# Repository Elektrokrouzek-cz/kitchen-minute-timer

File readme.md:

# Kitchen minute timer
This is the construction of simple kitchen minute timer based on logical 
circuits (4060, 4040, 4081 and 2x 4017). It was designed for beginners to 
train SMD components soldering (all passive components have 1206 packages).

PCB is 4-layer and was designed using KiCad 8. Fabrication output for JLCPCB is in gerber folder.

Happy soldering!

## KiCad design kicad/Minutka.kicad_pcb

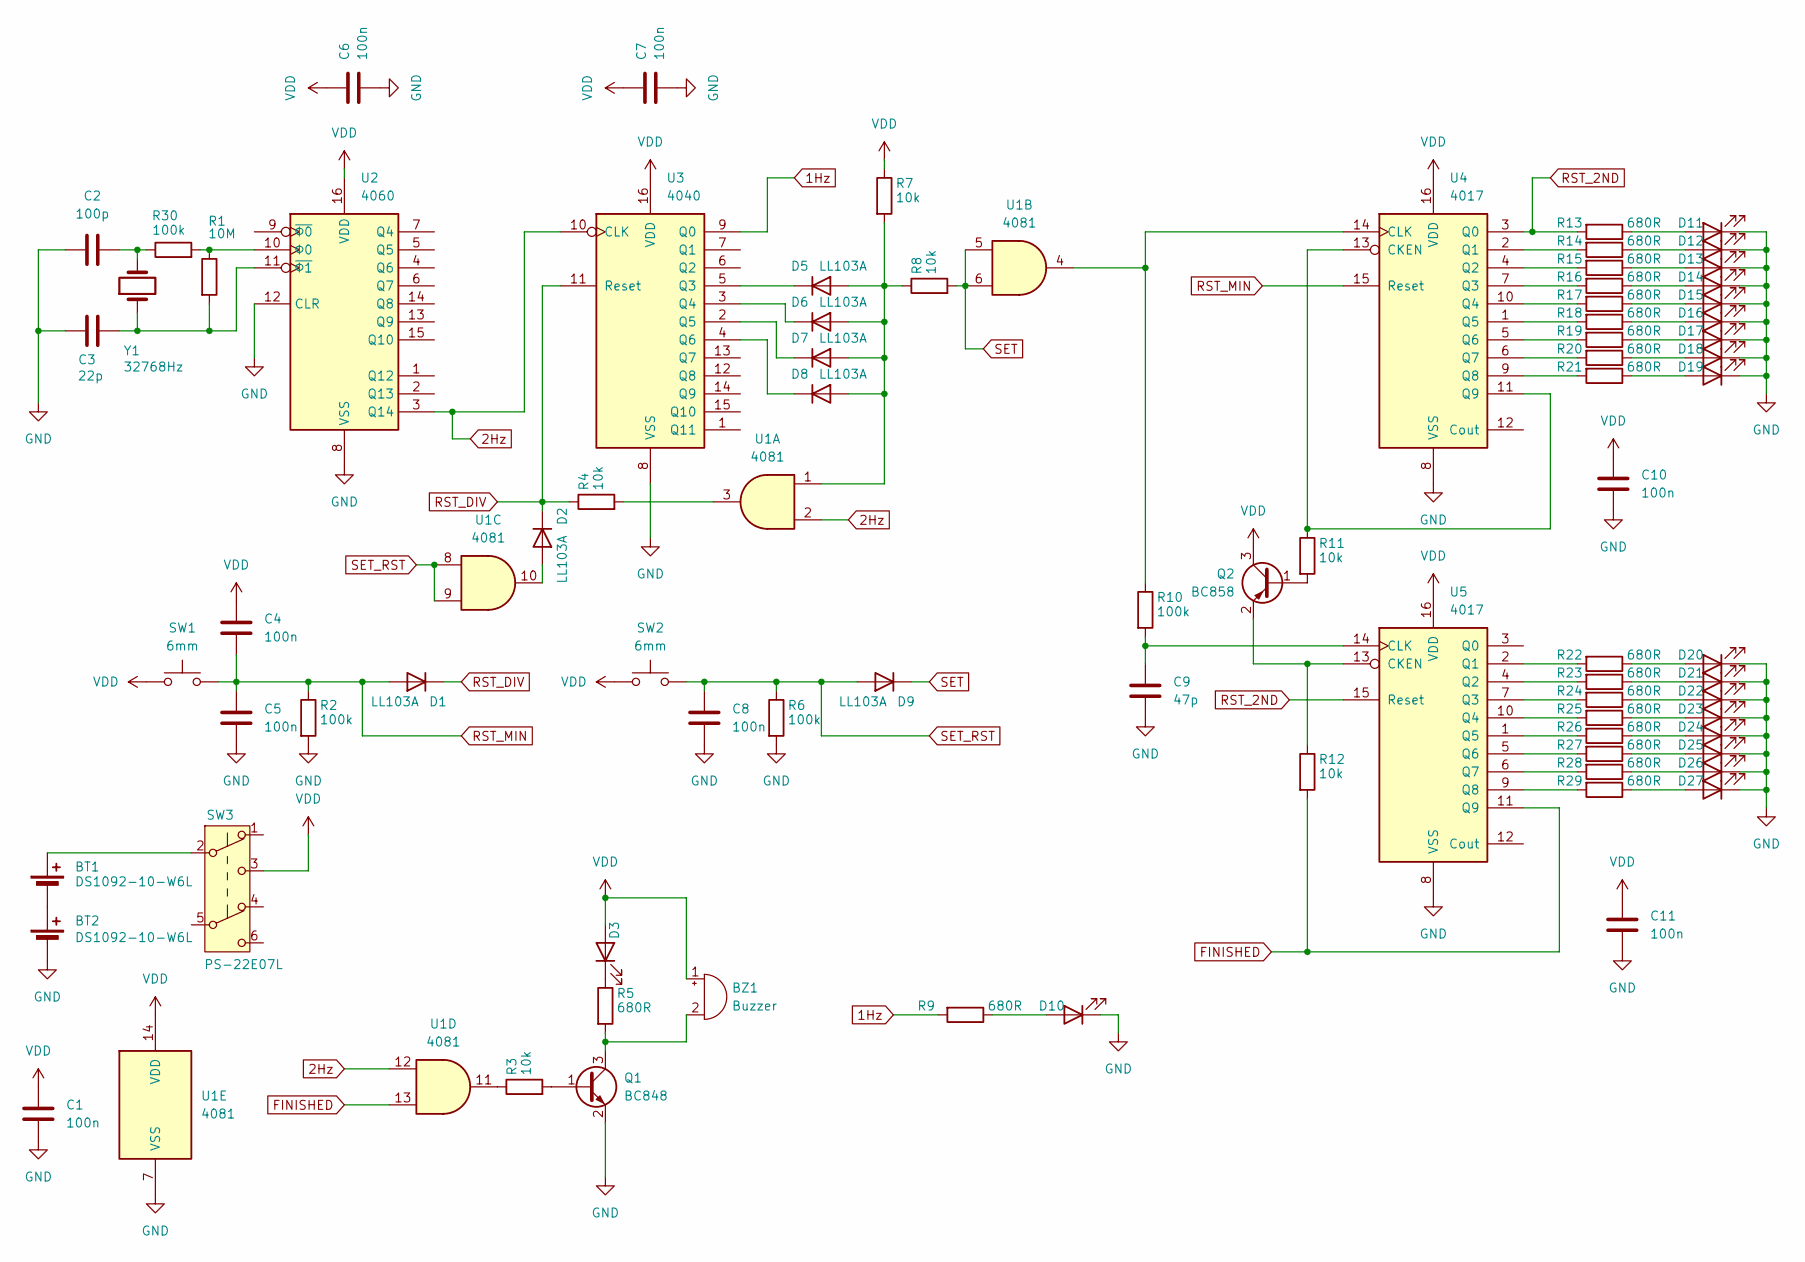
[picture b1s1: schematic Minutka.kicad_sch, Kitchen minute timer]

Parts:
BT1, BT2: DS1092-10-W6L; BatteryHolder_Renata_SMTU2032-LF_1x2032
BZ1: Buzzer; MagneticBuzzer_ProSignal_ABI-010-RC
C1, C4, C5, C6, C7, C8, C10, C11: 100n; C_1206_3216Metric_Pad1.33x1.80mm_HandSolder
C2: 100p; C_1206_3216Metric_Pad1.33x1.80mm_HandSolder
C3: 22p; C_1206_3216Metric_Pad1.33x1.80mm_HandSolder
C9: 47p; C_1206_3216Metric_Pad1.33x1.80mm_HandSolder
D1, D2, D5, D6, D7, D8, D9: LL103A; D_MiniMELF
D3: 3mm R; LED_D3.0mm
D10: 3mm Y; LED_D3.0mm
D11, D12, D13, D14, D15, D16, D17, D18, D19, D20, D21, D22, D23, D24, D25, D26, D27: 3mm G; LED_D3.0mm
Q1: BC848; SOT-23
Q2: BC858; SOT-23
R1: 10M; R_1206_3216Metric_Pad1.30x1.75mm_HandSolder
R2, R6, R10, R30: 100k; R_1206_3216Metric_Pad1.30x1.75mm_HandSolder
R3, R4, R7, R8, R11, R12: 10k; R_1206_3216Metric_Pad1.30x1.75mm_HandSolder
R5, R9, R13, R14, R15, R16, R17, R18, R19, R20, R21, R22, R23, R24, R25, R26, R27, R28, R29: 680R; R_1206_3216Metric_Pad1.30x1.75mm_HandSolder
SW1, SW2: 6mm; SW_PUSH_6mm_H13mm
SW3: PS-22E07L; SW_DPDT_7x7_Turbo
U1: 4081; SO-14_3.9x8.65mm_P1.27mm
U2: 4060; SO-16_3.9x9.9mm_P1.27mm
U3: 4040; SO-16_3.9x9.9mm_P1.27mm
U4, U5: 4017; SO-16_3.9x9.9mm_P1.27mm
Y1: 32768Hz; Crystal_AT310_D3.0mm_L10.0mm_Horizontal

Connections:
1Hz: R9.2, U3.9 (Q0)
2Hz: U1.2, U1.12, U2.3 (Q14), U3.10 (CLK)
FINISHED: R12.2, U1.13, U5.11 (Q9)
GND: BT2.2 (-), C1.1, C2.1, C3.1, C5.1, C6.1, C7.1, C8.1, C9.1, C10.1, C11.1, D10.1 (K), D11.1 (K), D12.1 (K), D13.1 (K), D14.1 (K), D15.1 (K), D16.1 (K), D17.1 (K), D18.1 (K), D19.1 (K), D20.1 (K), D21.1 (K), D22.1 (K), D23.1 (K), D24.1 (K), D25.1 (K), D26.1 (K), D27.1 (K), Q1.2 (E), R2.2, R6.2, U1.7 (VSS), U2.8 (VSS), U2.12 (CLR), U3.8 (VSS), U4.8 (VSS), U5.8 (VSS)
unnamed: BT1.1 (+), SW3.2 (B)
unnamed: BT1.2 (-), BT2.1 (+)
unnamed: BZ1.2 (-), Q1.3 (C), R5.2
unnamed: C2.2, R30.1, Y1.2
unnamed: D2.2 (A), U1.10
unnamed: D3.1 (K), R5.1
unnamed: D5.2 (A), D6.2 (A), D7.2 (A), D8.2 (A), R7.2, R8.1, U1.1
unnamed: D5.1 (K), U3.5 (Q3)
unnamed: D6.1 (K), U3.3 (Q4)
unnamed: D7.1 (K), U3.2 (Q5)
unnamed: D8.1 (K), U3.4 (Q6)
unnamed: D10.2 (A), R9.1
unnamed: D11.2 (A), R13.1
unnamed: D12.2 (A), R14.1
unnamed: D13.2 (A), R15.1
unnamed: D14.2 (A), R16.1
unnamed: D15.2 (A), R17.1
unnamed: D16.2 (A), R18.1
unnamed: D17.2 (A), R19.1
unnamed: D18.2 (A), R20.1
unnamed: D19.2 (A), R21.1
unnamed: D20.2 (A), R22.1
unnamed: D21.2 (A), R23.1
unnamed: D22.2 (A), R24.1
unnamed: D23.2 (A), R25.1
unnamed: D24.2 (A), R26.1
unnamed: D25.2 (A), R27.1
unnamed: D26.2 (A), R28.1
unnamed: D27.2 (A), R29.1
unnamed: Q1.1 (B), R3.2
unnamed: Q2.1 (B), R11.2
unnamed: Q2.2 (E), R12.1, U5.13 (CKEN)
unnamed: R3.1, U1.11
unnamed: R4.2, U1.3
unnamed: C3.2, R1.2, U2.11 (~Φ1), Y1.1
unnamed: R1.1, R30.2, U2.10 (Φ0)
unnamed: R11.1, U4.11 (Q9), U4.13 (CKEN)
unnamed: R10.1, U1.4, U4.14 (CLK)
unnamed: R14.2, U4.2 (Q1)
unnamed: R15.2, U4.4 (Q2)
unnamed: R16.2, U4.7 (Q3)
unnamed: R17.2, U4.10 (Q4)
unnamed: R18.2, U4.1 (Q5)
unnamed: R19.2, U4.5 (Q6)
unnamed: R20.2, U4.6 (Q7)
unnamed: R21.2, U4.9 (Q8)
unnamed: C9.2, R10.2, U5.14 (CLK)
unnamed: R22.2, U5.2 (Q1)
unnamed: R23.2, U5.4 (Q2)
unnamed: R24.2, U5.7 (Q3)
unnamed: R25.2, U5.10 (Q4)
unnamed: R26.2, U5.1 (Q5)
unnamed: R27.2, U5.5 (Q6)
unnamed: R28.2, U5.6 (Q7)
unnamed: R29.2, U5.9 (Q8)
RST_2ND: R13.2, U4.3 (Q0), U5.15 (Reset)
RST_DIV: D1.1 (K), D2.1 (K), R4.1, U3.11 (Reset)
RST_MIN: C4.1, C5.2, D1.2 (A), R2.1, SW1.2, U4.15 (Reset)
SET: D9.1 (K), R8.2, U1.5, U1.6
SET_RST: C8.2, D9.2 (A), R6.1, SW2.2, U1.8, U1.9
VDD: BZ1.1 (+), C1.2, C4.2, C6.2, C7.2, C10.2, C11.2, D3.2 (A), Q2.3 (C), R7.1, SW1.1, SW2.1, SW3.3 (C), U1.14 (VDD), U2.16 (VDD), U3.16 (VDD), U4.16 (VDD), U5.16 (VDD)

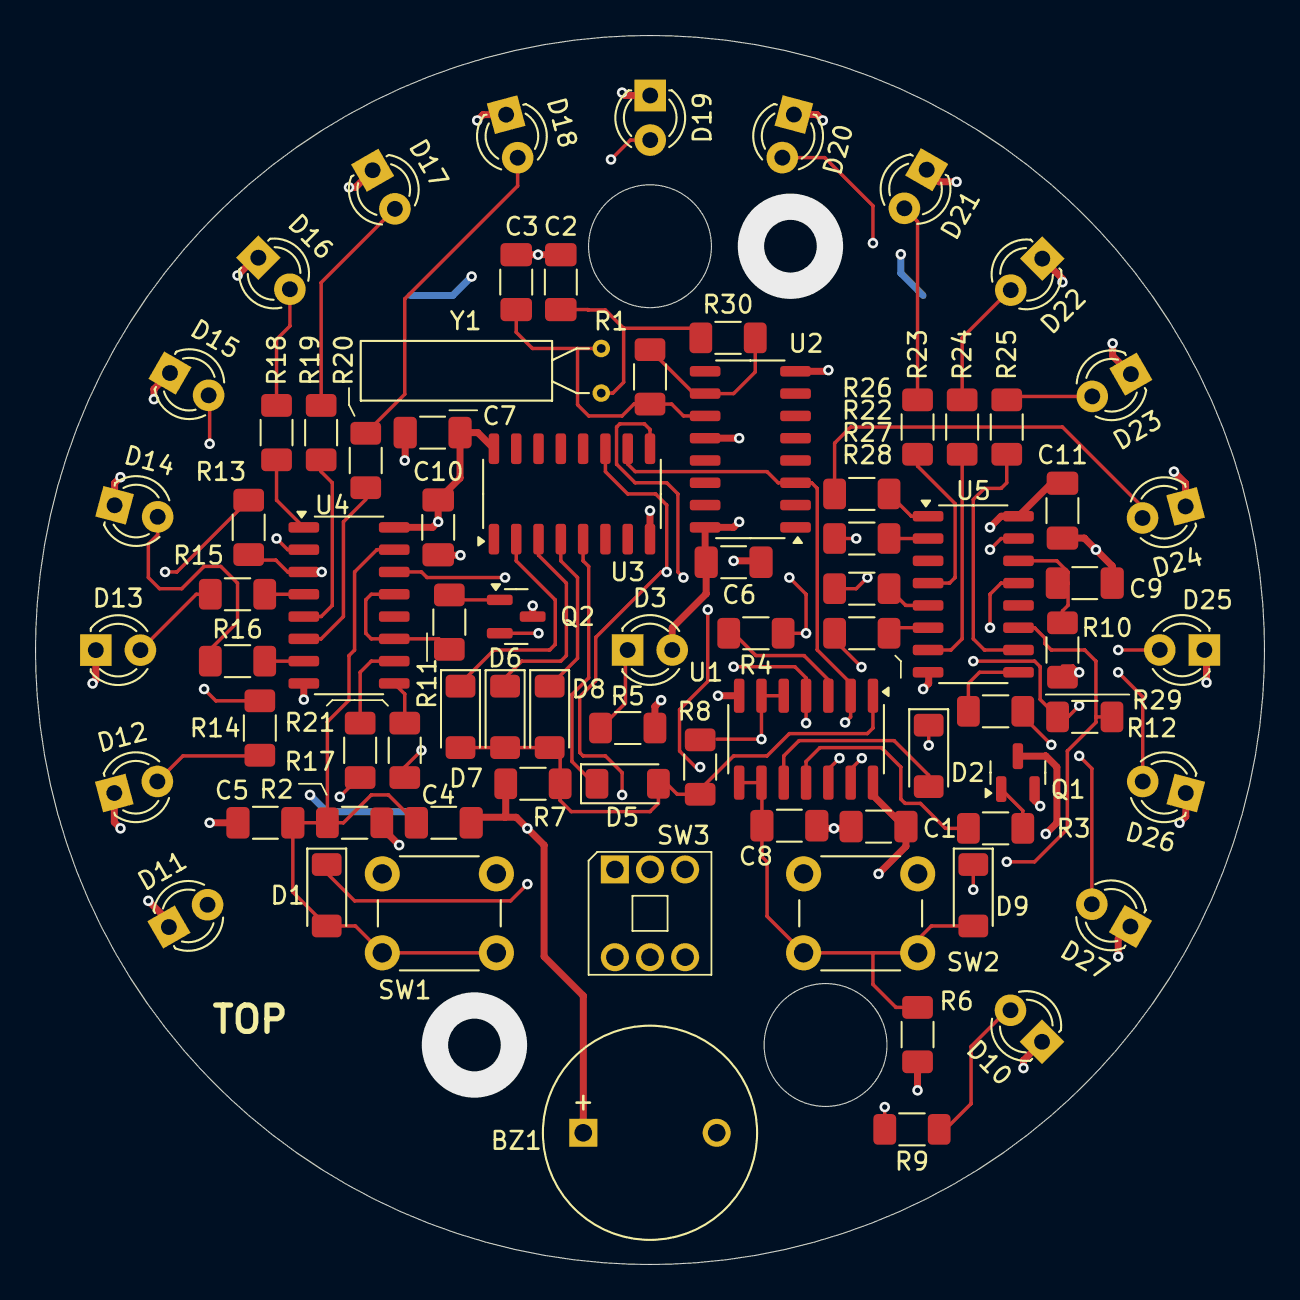
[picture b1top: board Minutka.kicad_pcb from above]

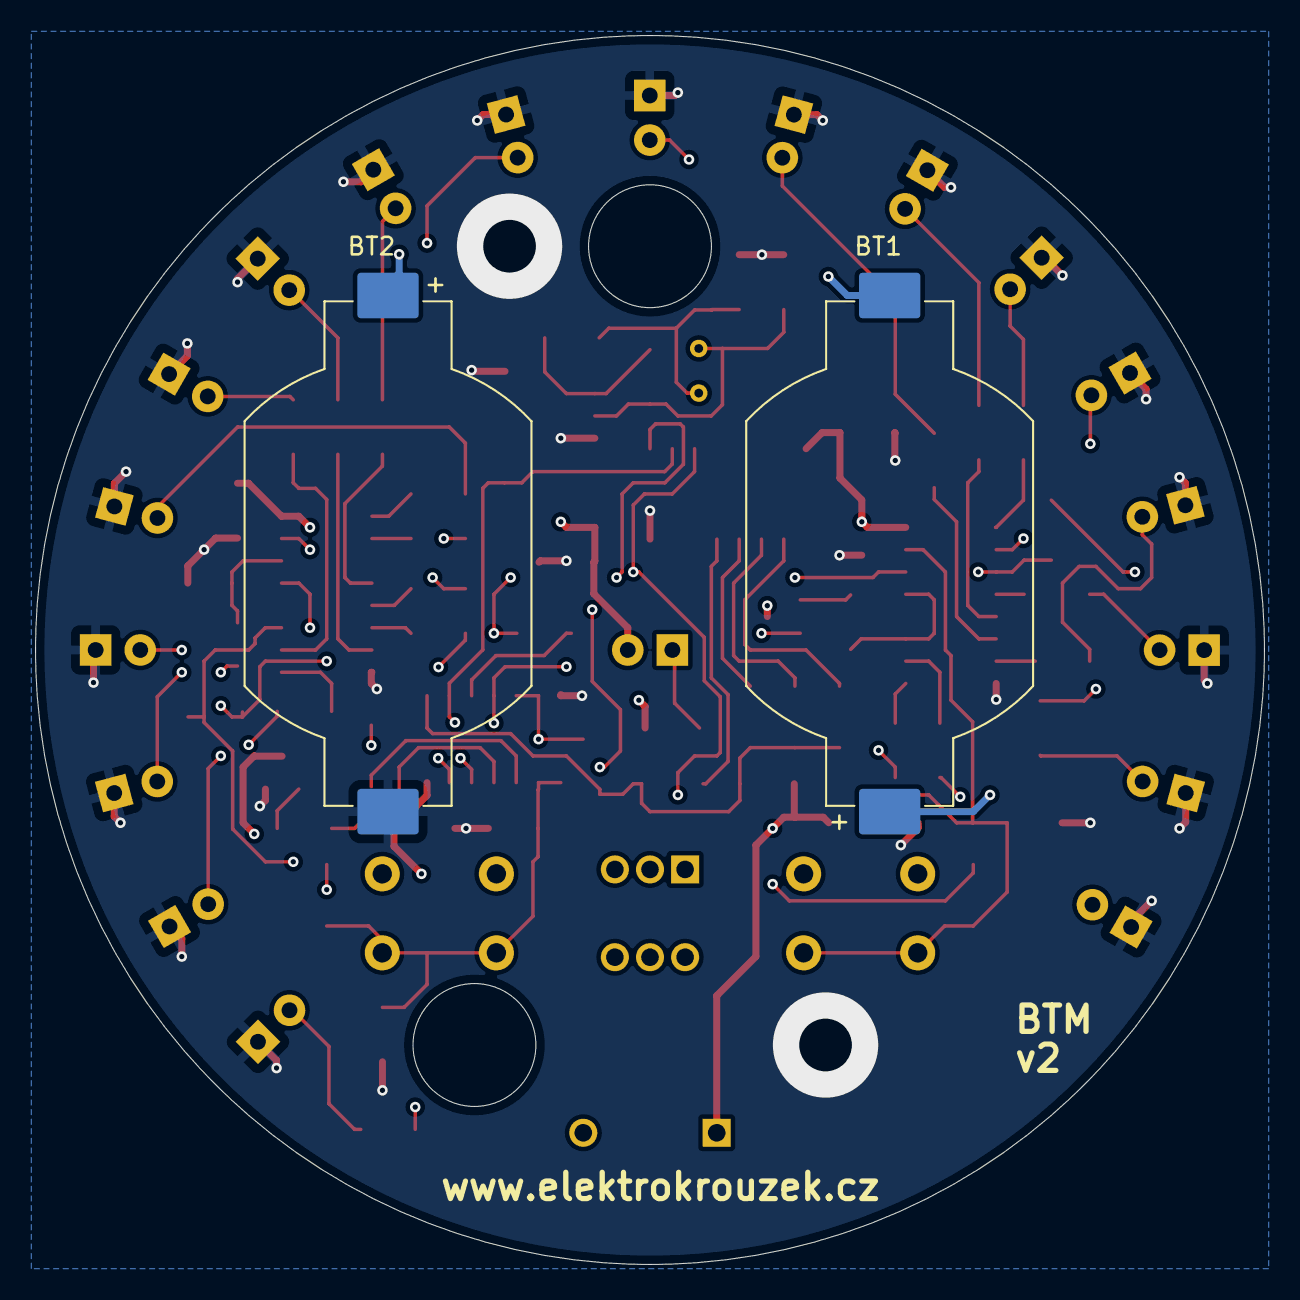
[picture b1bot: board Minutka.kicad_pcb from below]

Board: 4 copper layers, 70.0 x 70.0 mm, 81 parts (2 on the bottom side), 65 nets.

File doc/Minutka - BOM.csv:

"Reference","Value","Footprint","Qty","DNP"
"BT1,BT2","DS1092-10-W6L","Battery:BatteryHolder_Renata_SMTU2032-LF_1x2032","2",""
"BZ1","Buzzer","Buzzer_Beeper:MagneticBuzzer_ProSignal_ABI-010-RC","1",""
"C1,C4,C5,C6,C7,C8,C10,C11","100n","Capacitor_SMD:C_1206_3216Metric_Pad1.33x1.80mm_HandSolder","8",""
"C2","100p","Capacitor_SMD:C_1206_3216Metric_Pad1.33x1.80mm_HandSolder","1",""
"C3","22p","Capacitor_SMD:C_1206_3216Metric_Pad1.33x1.80mm_HandSolder","1",""
"C9","47p","Capacitor_SMD:C_1206_3216Metric_Pad1.33x1.80mm_HandSolder","1",""
"D1,D2,D5,D6,D7,D8,D9","LL103A","Diode_SMD:D_MiniMELF","7",""
"D3","3mm R","LED_THT:LED_D3.0mm","1",""
"D10","3mm Y","LED_THT:LED_D3.0mm","1",""
"D11,D12,D13,D14,D15,D16,D17,D18,D19,D20,D21,D22,D23,D24,D25,D26,D27","3mm G","LED_THT:LED_D3.0mm","17",""
"Q1","BC848","Package_TO_SOT_SMD:SOT-23","1",""
"Q2","BC858","Package_TO_SOT_SMD:SOT-23","1",""
"R1","10M","Resistor_SMD:R_1206_3216Metric_Pad1.30x1.75mm_HandSolder","1",""
"R2,R6,R10,R30","100k","Resistor_SMD:R_1206_3216Metric_Pad1.30x1.75mm_HandSolder","4",""
"R3,R4,R7,R8,R11,R12","10k","Resistor_SMD:R_1206_3216Metric_Pad1.30x1.75mm_HandSolder","6",""
"R5,R9,R13,R14,R15,R16,R17,R18,R19,R20,R21,R22,R23,R24,R25,R26,R27,R28,R29","680R","Resistor_SMD:R_1206_3216Metric_Pad1.30x1.75mm_HandSolder","19",""
"SW1,SW2","6mm","Button_Switch_THT:SW_PUSH_6mm_H13mm","2",""
"SW3","PS-22E07L","Button_Switch_THT_Hap:SW_DPDT_7x7_Turbo","1",""
"U1","4081","Package_SO:SO-14_3.9x8.65mm_P1.27mm","1",""
"U2","4060","Package_SO:SO-16_3.9x9.9mm_P1.27mm","1",""
"U3","4040","Package_SO:SO-16_3.9x9.9mm_P1.27mm","1",""
"U4,U5","4017","Package_SO:SO-16_3.9x9.9mm_P1.27mm","2",""
"Y1","32768Hz","Crystal:Crystal_AT310_D3.0mm_L10.0mm_Horizontal","1",""

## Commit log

2024-12-27 LED 3D model changes (color)
2024-12-27 Preliminary 3D model
2025-02-07 Final 3D models, manuals added
